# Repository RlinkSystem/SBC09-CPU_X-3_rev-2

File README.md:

# SBC09-CPU_X-3_rev-2

Simple SBC design around MC6809 Revision 2

This was the fist atemp/test to make a full SBC system based on my old
modem X-3 construction.

This was done during Christmas weekend 2024.
To test my simple & basic setup, to start expermenting.

My goal is to have an uncomplex build
* but not with a few large ICs
* not with PAL/GAL

So my setup is:
* CPU: MC6809
* MEM: 6x HM6264ALP-15
* ROM: 2764 eq EPROM / EEPROM
* PTM: MC6840
* ACIA: 2x MC6850
* ACIA: R6551
* PIA: 3x MC6821
* Glue logic:
  * 74HCT04
  * 74HCT138
  * <del>74HCT154</del> 74HCT138

My testing setup:

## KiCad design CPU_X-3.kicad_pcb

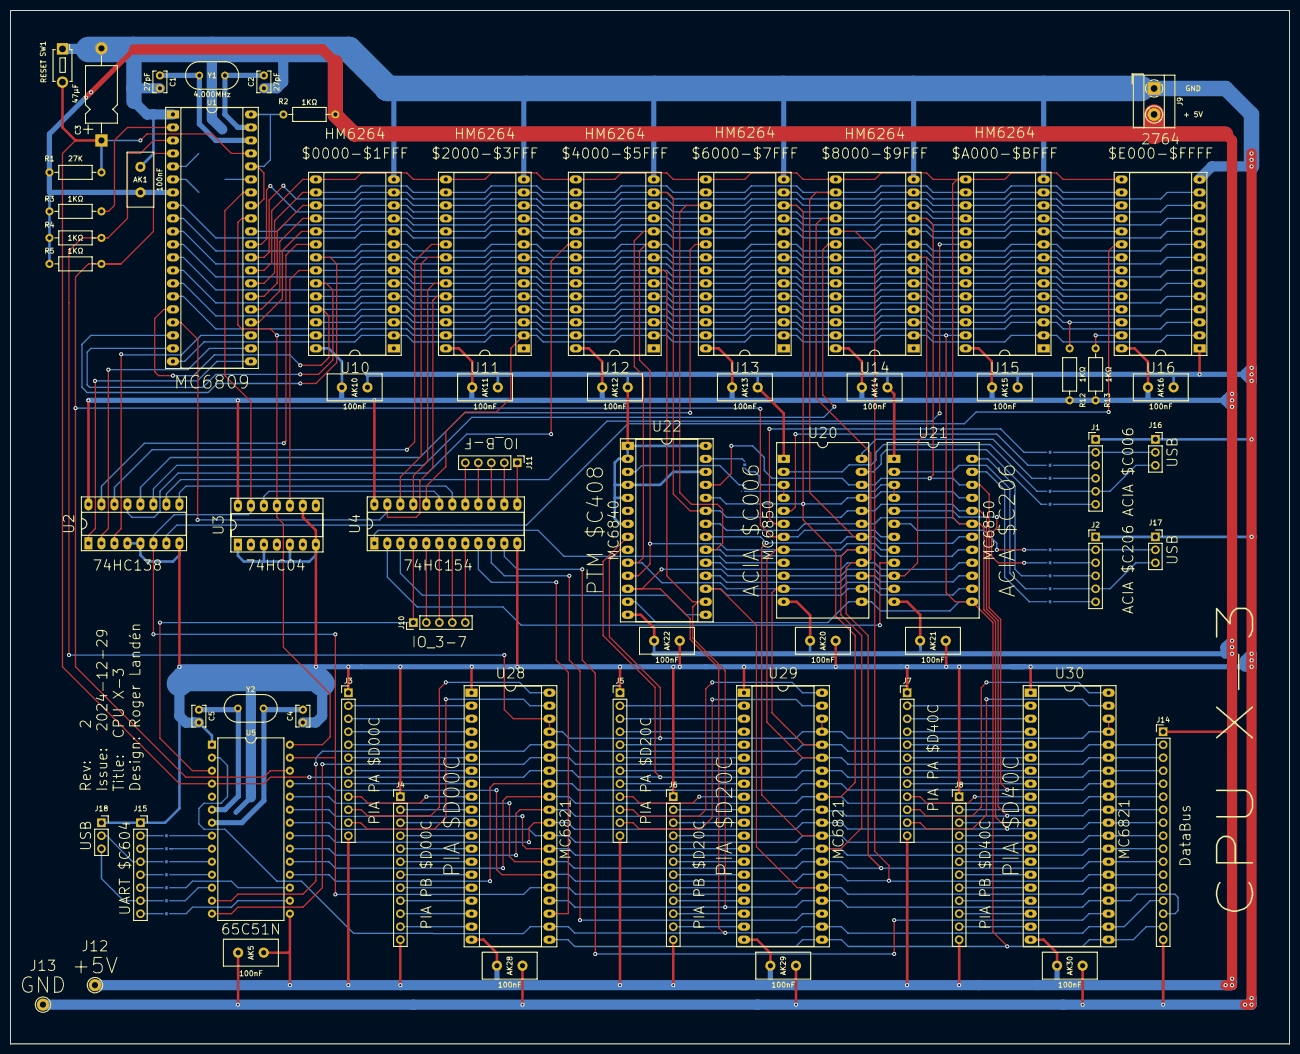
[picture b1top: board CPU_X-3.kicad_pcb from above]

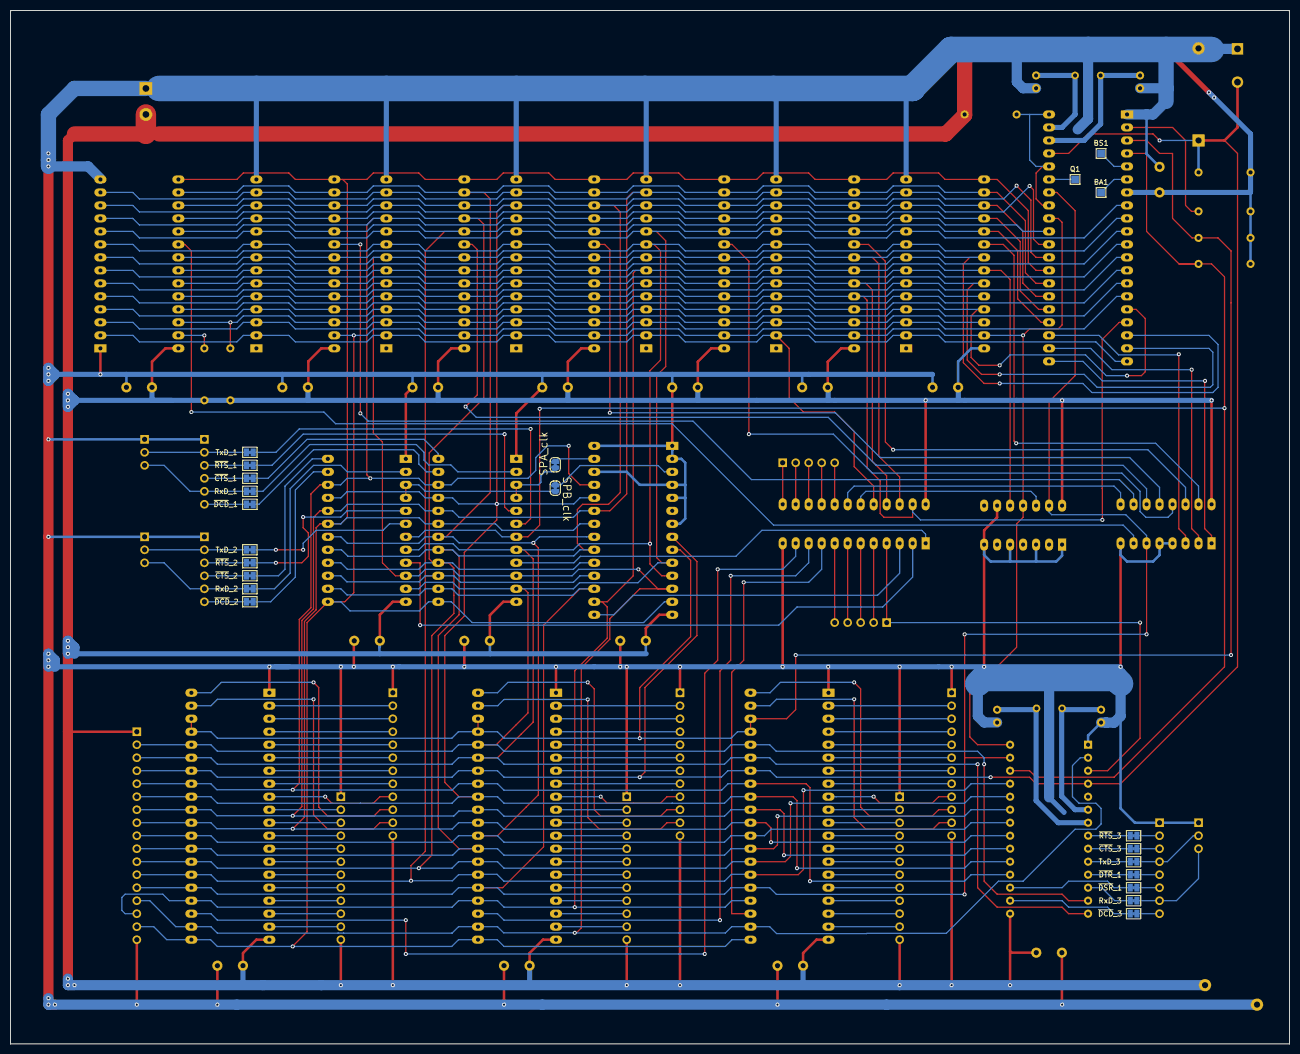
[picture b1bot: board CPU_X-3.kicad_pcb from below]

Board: 2 copper layers, 250.0 x 202.0 mm, 77 parts (11 on the bottom side), 144 nets.

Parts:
AK1, AK5, AK10, AK11, AK12, AK13, AK14, AK15, AK16, AK20, AK21, AK22, AK28, AK29, AK30: 100nF; Avkopplings_C
BA1: BA; TestPoint_Pad_1.5x1.5mm
BS1: BS; TestPoint_Pad_1.5x1.5mm
C1, C2, C4, C5: 27pF; C_Rect_L4.0mm_W2.5mm_P2.50mm
C3: 47µF; CP_Axial_L11.0mm_D6.0mm_P18.00mm_Horizontal
J1: UART $C006; PinHeader_1x06_P2.54mm_Vertical
J2: UART $C206; PinHeader_1x06_P2.54mm_Vertical
J3: PA U28; PinHeader_1x12_P2.54mm_Vertical
J4: PB U28; PinHeader_1x12_P2.54mm_Vertical
J5: PA U29; PinHeader_1x12_P2.54mm_Vertical
J6: PB U29; PinHeader_1x12_P2.54mm_Vertical
J7: PA U30; PinHeader_1x12_P2.54mm_Vertical
J8: PB U30; PinHeader_1x12_P2.54mm_Vertical
J9: POWER; TerminalBlock_MetzConnect_Type101_RT01602HBWC_1x02_P5.08mm_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
J10: IO_3-7; PinHeader_1x05_P2.54mm_Vertical
J11: IO_B-F; PinHeader_1x05_P2.54mm_Vertical
J12: +5V; Pin_D1.0mm_L10.0mm_LooseFit
J13: GND; Pin_D1.0mm_L10.0mm_LooseFit
J14: DataBus; PinHeader_1x17_P2.54mm_Vertical
J15: UART $C604; PinSocket_1x08_P2.54mm_Vertical
J16, J17, J18: USB; PinSocket_1x03_P2.54mm_Vertical
Q1: Q; TestPoint_Pad_1.5x1.5mm
R1: 27K; R_Axial_DIN0207_L6.3mm_D2.5mm_P10.16mm_Horizontal
R2, R3, R4, R5, R13: 1KΩ; R_Axial_DIN0207_L6.3mm_D2.5mm_P10.16mm_Horizontal
R12: 1KΩ; R_Axial_PullUp_long
RxD_1: UART-A; SolderJumper-2_P1.3mm_Bridged_Pad1.0x1.5mm
RxD_2: UART-B; SolderJumper-2_P1.3mm_Bridged_Pad1.0x1.5mm
RxD_3: UART-C; SolderJumper-2_P1.3mm_Bridged_Pad1.0x1.5mm
SW1: RESET; SW_PUSH_1P1T_6x3.5mm_H5.0_APEM_MJTP1250
TxD_1: UART-A; SolderJumper-2_P1.3mm_Bridged_Pad1.0x1.5mm
TxD_2: UART-B; SolderJumper-2_P1.3mm_Bridged_Pad1.0x1.5mm
TxD_3: UART-C; SolderJumper-2_P1.3mm_Bridged_Pad1.0x1.5mm
U1: MC6809; DIP-40_W15.24mm_Socket_LongPads
U2: 74HC138; DIP-16_W7.62mm_Socket_LongPads
U3: 74HC04; DIP-14_W7.62mm_Socket_LongPads
U4: 74HC154; DIP-24_W7.62mm_Socket_LongPads
U5: 65C51N; DIP-28_W15.24mm
U10, U11, U12, U13, U14, U15: HM6264; X3-MEM_DIP-28
U16: 2764; X3-MEM_DIP-28
U20, U21: MC6850; DIP-24_18.0mmx34.29mm_W15.24mm_Socket_LongPads
U22: MC6840; DIP-28_W15.24mm_Socket_LongPads
U28, U29, U30: MC6821; X3-IO_DIP-40
Y1: 4.000MHz; Resonator-2Pin_W10.0mm_H5.0mm
Y2: 1.8432MHz; Resonator-2Pin_W10.0mm_H5.0mm
clk_RS1: SPA_clk; SolderJumper-2_P1.3mm_Bridged_RoundedPad1.0x1.5mm
clk_RS2: SPB_clk; SolderJumper-2_P1.3mm_Bridged_RoundedPad1.0x1.5mm

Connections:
+5V: AK1.1, AK5.1, AK10.1, AK11.1, AK12.1, AK13.1, AK14.1, AK15.1, AK16.1, AK20.1, AK21.1, AK22.1, AK28.1, AK29.1, AK30.1, J3.12, J4.12, J5.12, J6.12, J7.12, J8.12, J9.2, J12.1, J14.1, R1.1, R2.1, R3.1, R4.1, R5.1, R12.1, R13.1, U1.7 (VCC), U2.16 (VCC), U3.14 (VCC), U4.24 (VCC), U5.15 (VDD), U10.28 (VCC), U11.28 (VCC), U12.28 (VCC), U13.28 (VCC), U14.28 (VCC), U15.28 (VCC), U16.28 (VCC), U20.12 (VCC), U21.12 (VCC), U22.14 (VCC), U28.20 (VCC), U29.20 (VCC), U30.20 (VCC)
/$00: U2.15 (~Y0), U10.20 (~CS1)
/$20: U2.14 (~Y1), U11.20 (~CS1)
/$40: U2.13 (~Y2), U12.20 (~CS1)
/$60: U2.12 (~Y3), U13.20 (~CS1)
/$80: U2.11 (~Y4), U14.20 (~CS1)
/$A0: U2.10 (~Y5), U15.20 (~CS1)
/$C0: U2.9 (~Y6), U4.18 (~E0)
/$E0: U2.7 (~Y7), U16.20 (~CE)
/A0: J14.2, U1.8 (A0), U5.13 (RS0), U10.10 (A0), U11.10 (A0), U12.10 (A0), U13.10 (A0), U14.10 (A0), U15.10 (A0), U16.10 (A0), U20.11 (RS), U21.11 (RS), U22.10 (RS0), U28.36 (RS0), U29.36 (RS0), U30.36 (RS0)
/A1: J14.3, U1.9 (A1), U5.14 (RS1), U10.9 (A1), U11.9 (A1), U12.9 (A1), U13.9 (A1), U14.9 (A1), U15.9 (A1), U16.9 (A1), U20.8 (CS0), U21.8 (CS0), U22.11 (RS1), U28.35 (RS1), U29.35 (RS1), U30.35 (RS1)
/A2: J14.14, U1.10 (A2), U5.2 (CS0), U10.8 (A2), U11.8 (A2), U12.8 (A2), U13.8 (A2), U14.8 (A2), U15.8 (A2), U16.8 (A2), U20.10 (CS1), U21.10 (CS1), U22.12 (RS2), U28.22 (CS0), U29.22 (CS0), U30.22 (CS0)
/A3: J14.15, U1.11 (A3), U10.7 (A3), U11.7 (A3), U12.7 (A3), U13.7 (A3), U14.7 (A3), U15.7 (A3), U16.7 (A3), U22.16 (CS1), U28.24 (CS1), U29.24 (CS1), U30.24 (CS1)
/A4: U1.12 (A4), U10.6 (A4), U11.6 (A4), U12.6 (A4), U13.6 (A4), U14.6 (A4), U15.6 (A4), U16.6 (A4)
/A5: U1.13 (A5), U10.5 (A5), U11.5 (A5), U12.5 (A5), U13.5 (A5), U14.5 (A5), U15.5 (A5), U16.5 (A5)
/A6: U1.14 (A6), U10.4 (A6), U11.4 (A6), U12.4 (A6), U13.4 (A6), U14.4 (A6), U15.4 (A6), U16.4 (A6)
/A7: U1.15 (A7), U10.3 (A7), U11.3 (A7), U12.3 (A7), U13.3 (A7), U14.3 (A7), U15.3 (A7), U16.3 (A7)
/A8: U1.16 (A8), U10.25 (A8), U11.25 (A8), U12.25 (A8), U13.25 (A8), U14.25 (A8), U15.25 (A8), U16.25 (A8)
/A9: U1.17 (A9), U4.23 (A0), U10.24 (A9), U11.24 (A9), U12.24 (A9), U13.24 (A9), U14.24 (A9), U15.24 (A9), U16.24 (A9)
/A10: U1.18 (A10), U4.22 (A1), U10.21 (A10), U11.21 (A10), U12.21 (A10), U13.21 (A10), U14.21 (A10), U15.21 (A10), U16.21 (A10)
/A11: U1.19 (A11), U4.21 (A2), U10.23 (A11), U11.23 (A11), U12.23 (A11), U13.23 (A11), U14.23 (A11), U15.23 (A11), U16.23 (A11)
/A12: U1.20 (A12), U4.20 (A3), U10.2 (A12), U11.2 (A12), U12.2 (A12), U13.2 (A12), U14.2 (A12), U15.2 (A12), U16.2 (A12)
/CA11: J5.10, U29.40 (CA1)
/CA12: J5.11, U29.39 (CA2)
/CA21: J3.10, U28.40 (CA1)
/CA22: J3.11, U28.39 (CA2)
/CA31: J7.10, U30.40 (CA1)
/CA32: J7.11, U30.39 (CA2)
/CB11: J6.10, U29.18 (CB1)
/CB12: J6.11, U29.19 (CB2)
/CB21: J4.10, U28.18 (CB1)
/CB22: J4.11, U28.19 (CB2)
/CB31: J8.10, U30.18 (CB1)
/CB32: J8.11, U30.19 (CB2)
/D0: J14.5, U1.31 (D0), U5.18 (D0), U10.11 (I/O0), U11.11 (I/O0), U12.11 (I/O0), U13.11 (I/O0), U14.11 (I/O0), U15.11 (I/O0), U16.11 (D0), U20.22 (D0), U21.22 (D0), U22.25 (D0), U28.33 (D0), U29.33 (D0), U30.33 (D0)
/D1: J14.6, U1.30 (D1), U5.19 (D1), U10.12 (I/O1), U11.12 (I/O1), U12.12 (I/O1), U13.12 (I/O1), U14.12 (I/O1), U15.12 (I/O1), U16.12 (D1), U20.21 (D1), U21.21 (D1), U22.24 (D1), U28.32 (D1), U29.32 (D1), U30.32 (D1)
/D2: J14.7, U1.29 (D2), U5.20 (D2), U10.13 (I/O2), U11.13 (I/O2), U12.13 (I/O2), U13.13 (I/O2), U14.13 (I/O2), U15.13 (I/O2), U16.13 (D2), U20.20 (D2), U21.20 (D2), U22.23 (D2), U28.31 (D2), U29.31 (D2), U30.31 (D2)
/D3: J14.8, U1.28 (D3), U5.21 (D3), U10.15 (I/O3), U11.15 (I/O3), U12.15 (I/O3), U13.15 (I/O3), U14.15 (I/O3), U15.15 (I/O3), U16.15 (D3), U20.19 (D3), U21.19 (D3), U22.22 (D3), U28.30 (D3), U29.30 (D3), U30.30 (D3)
/D4: J14.9, U1.27 (D4), U5.22 (D4), U10.16 (I/O4), U11.16 (I/O4), U12.16 (I/O4), U13.16 (I/O4), U14.16 (I/O4), U15.16 (I/O4), U16.16 (D4), U20.18 (D4), U21.18 (D4), U22.21 (D4), U28.29 (D4), U29.29 (D4), U30.29 (D4)
/D5: J14.10, U1.26 (D5), U5.23 (D5), U10.17 (I/O5), U11.17 (I/O5), U12.17 (I/O5), U13.17 (I/O5), U14.17 (I/O5), U15.17 (I/O5), U16.17 (D5), U20.17 (D5), U21.17 (D5), U22.20 (D5), U28.28 (D5), U29.28 (D5), U30.28 (D5)
/D6: J14.11, U1.25 (D6), U5.24 (D6), U10.18 (I/O6), U11.18 (I/O6), U12.18 (I/O6), U13.18 (I/O6), U14.18 (I/O6), U15.18 (I/O6), U16.18 (D6), U20.16 (D6), U21.16 (D6), U22.19 (D6), U28.27 (D6), U29.27 (D6), U30.27 (D6)
/D7: J14.12, U1.24 (D7), U5.25 (D7), U10.19 (I/O7), U11.19 (I/O7), U12.19 (I/O7), U13.19 (I/O7), U14.19 (I/O7), U15.19 (I/O7), U16.19 (D7), U20.15 (D7), U21.15 (D7), U22.18 (D7), U28.26 (D7), U29.26 (D7), U30.26 (D7)
/E-clock: J14.13, U1.34 (E), U2.6 (E2), U3.13, U5.27 (PHI2), U20.14 (E), U21.14 (E), U22.17 (E), U28.25 (ENABLE), U29.25 (ENABLE), U30.25 (ENABLE)
/PA10: J5.2, U29.2 (PA0)
/PA11: J5.3, U29.3 (PA1)
/PA12: J5.4, U29.4 (PA2)
/PA13: J5.5, U29.5 (PA3)
/PA14: J5.6, U29.6 (PA4)
/PA15: J5.7, U29.7 (PA5)
/PA16: J5.8, U29.8 (PA6)
/PA17: J5.9, U29.9 (PA7)
/PA20: J3.2, U28.2 (PA0)
/PA21: J3.3, U28.3 (PA1)
/PA22: J3.4, U28.4 (PA2)
/PA23: J3.5, U28.5 (PA3)
/PA24: J3.6, U28.6 (PA4)
/PA25: J3.7, U28.7 (PA5)
/PA26: J3.8, U28.8 (PA6)
/PA27: J3.9, U28.9 (PA7)
/PA30: J7.2, U30.2 (PA0)
/PA31: J7.3, U30.3 (PA1)
/PA32: J7.4, U30.4 (PA2)
/PA33: J7.5, U30.5 (PA3)
/PA34: J7.6, U30.6 (PA4)
/PA35: J7.7, U30.7 (PA5)
/PA36: J7.8, U30.8 (PA6)
/PA37: J7.9, U30.9 (PA7)
/PB10: J6.2, U29.10 (PB0)
/PB11: J6.3, U29.11 (PB1)
/PB12: J6.4, U29.12 (PB2)
/PB13: J6.5, U29.13 (PB3)
/PB14: J6.6, U29.14 (PB4)
/PB15: J6.7, U29.15 (PB5)
/PB16: J6.8, U29.16 (PB6)
/PB17: J6.9, U29.17 (PB7)
/PB20: J4.2, U28.10 (PB0)
/PB21: J4.3, U28.11 (PB1)
/PB22: J4.4, U28.12 (PB2)
/PB23: J4.5, U28.13 (PB3)
/PB24: J4.6, U28.14 (PB4)
/PB25: J4.7, U28.15 (PB5)
/PB26: J4.8, U28.16 (PB6)
/PB27: J4.9, U28.17 (PB7)
/PB30: J8.2, U30.10 (PB0)
/PB31: J8.3, U30.11 (PB1)
/PB32: J8.4, U30.12 (PB2)
/PB33: J8.5, U30.13 (PB3)
/PB34: J8.6, U30.14 (PB4)
/PB35: J8.7, U30.15 (PB5)
/PB36: J8.8, U30.16 (PB6)
/PB37: J8.9, U30.17 (PB7)
/PTM_o1: U22.27 (O1), clk_RS1.1 (A)
/PTM_o2: U22.3 (O2), clk_RS2.1 (A)
/SPA_RxD: J1.5, J16.3, RxD_1.2 (B)
/SPA_TxD: J1.2, J16.2, TxD_1.2 (B)
/SPB_RxD: J2.5, J17.3, RxD_2.2 (B)
/SPB_TxD: J2.2, J17.2, TxD_2.2 (B)
/SPC_RxD: J15.7, J18.3, RxD_3.2 (B)
/SPC_TxD: J15.4, J18.2, TxD_3.2 (B)
/clk_RS1: U20.3 (Rx_CLK), U20.4 (Tx_CLK), clk_RS1.2 (B)
/clk_RS2: U21.3 (Rx_CLK), U21.4 (Tx_CLK), clk_RS2.2 (B)
/~Read: U3.10, U10.22 (~OE), U11.22 (~OE), U12.22 (~OE), U13.22 (~OE), U14.22 (~OE), U15.22 (~OE), U16.22 (~OE)
/~Write: J14.16, U1.32 (R/~W), U3.11, U5.28 (R~W), U10.27 (~WE), U11.27 (~WE), U12.27 (~WE), U13.27 (~WE), U14.27 (~WE), U15.27 (~WE), U20.13 (R/~W), U21.13 (R/~W), U22.13 (R/~W), U28.21 (R/~W), U29.21 (R/~W), U30.21 (R/~W)
FIRQ: R5.2, U1.4 (~FIRQ), U5.26 (~IRQ), U20.7 (~IRQ), U21.7 (~IRQ)
GND: AK1.2, AK5.2, AK10.2, AK11.2, AK12.2, AK13.2, AK14.2, AK15.2, AK16.2, AK20.2, AK21.2, AK22.2, AK28.2, AK29.2, AK30.2, C1.2, C2.1, C3.2, C4.1, C5.2, J1.1, J2.1, J3.1, J4.1, J5.1, J6.1, J7.1, J8.1, J9.1, J13.1, J14.17, J15.1, J16.1, J17.1, J18.1, SW1.1, U1.1 (VSS), U2.4 (~E0), U2.5 (~E1), U2.8 (GND), U3.1, U3.3, U3.5, U3.7 (GND), U3.9, U4.12 (GND), U5.1 (VSS), U10.14 (GND), U11.14 (GND), U12.14 (GND), U13.14 (GND), U14.14 (GND), U15.14 (GND), U16.1 (VPP), U16.14 (GND), U20.1 (VSS), U21.1 (VSS), U22.1 (VSS), U22.2 (~G2), U22.4 (~C2), U22.5 (~G3), U22.7 (~C3), U22.26 (~G1), U22.28 (~C1), U28.1 (VSS), U29.1 (VSS), U30.1 (VSS)
IRQ: R4.2, U1.3 (~IRQ), U22.9 (~IRQ), U28.37 (~IRQB), U28.38 (~IRQA), U29.37 (~IRQB), U29.38 (~IRQA), U30.37 (~IRQB), U30.38 (~IRQA)
NMI: R3.2, U1.2 (~NMI)
unnamed: J10.1, U4.4 (~S3), U5.3 (~CS1)
unnamed: J10.2, U4.5 (~S4)
unnamed: J10.3, U4.6 (~S5)
unnamed: J10.4, U4.7 (~S6)
unnamed: J10.5, U4.8 (~S7)
unnamed: J11.1, U4.13 (~S11)
unnamed: J11.2, U4.14 (~S12)
unnamed: J11.3, U4.15 (~S13)
unnamed: J11.4, U4.16 (~S14)
unnamed: J11.5, U4.17 (~S15)
unnamed: RxD_1.1 (A), U20.2 (Rx_Data)
unnamed: RxD_2.1 (A), U21.2 (Rx_Data)
unnamed: RxD_3.1 (A), U5.12 (RxD)
unnamed: TxD_1.1 (A), U20.6 (Tx_Data)
unnamed: TxD_2.1 (A), U21.6 (Tx_Data)
unnamed: TxD_3.1 (A), U5.10 (TxD)
unnamed: U1.21 (A13), U2.1 (A0)
unnamed: U1.22 (A14), U2.2 (A1)
unnamed: U1.23 (A15), U2.3 (A2)
unnamed: BA1.1, U1.6 (BA)
unnamed: BS1.1, U1.5 (BS)
unnamed: C1.1, U1.38 (EXTAL), Y1.1
unnamed: R2.2, U1.33 (~DMA/BREQ), U1.36 (MRDY), U1.40 (~HALT)
unnamed: Q1.1, U1.35 (Q)
unnamed: C2.2, U1.39 (XTAL), Y1.2
unnamed: U3.12, U4.19 (~E1)
unnamed: C5.1, U5.6 (XTLI), Y2.1
unnamed: C4.2, U5.7 (XTLO), Y2.2
unnamed: R12.2, U10.26 (CS2), U11.26 (CS2), U12.26 (CS2), U13.26 (CS2), U14.26 (CS2), U15.26 (CS2), U16.26 (NC)
unnamed: R13.2, U16.27 (~PGM)
unnamed: U4.1 (~S0), U20.9 (~CS2)
unnamed: U4.2 (~S1), U21.9 (~CS2)
unnamed: U4.3 (~S2), U22.15 (~CS0)
unnamed: U4.9 (~S8), U28.23 (~CS2)
unnamed: U4.10 (~S9), U29.23 (~CS2)
unnamed: U4.11 (~S10), U30.23 (~CS2)
~RESET: C3.1, J14.4, R1.2, SW1.2, U1.37 (~RESET), U5.4 (~RES), U22.8 (~RESET), U28.34 (~RESET), U29.34 (~RESET), U30.34 (~RESET)

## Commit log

2025-09-09 Added the KiCAD of CPU X-3 rev 2
2025-09-09 Add PCB card picture
2025-09-09 Readme picture
